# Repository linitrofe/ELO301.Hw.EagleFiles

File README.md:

# ELO301.Hw.EagleFiles
Repositorio dedicado a compartir archivos con el curso ELO301 dictado por el Departamento de Ingeniería Electrónica de la Universidad Técnica Federico Santa María
Se adjunta detalle de los contenidos:
- Carpeta Libraries/ contiene librerías de Autodesk Eagle provistas para su uso en el ramo.

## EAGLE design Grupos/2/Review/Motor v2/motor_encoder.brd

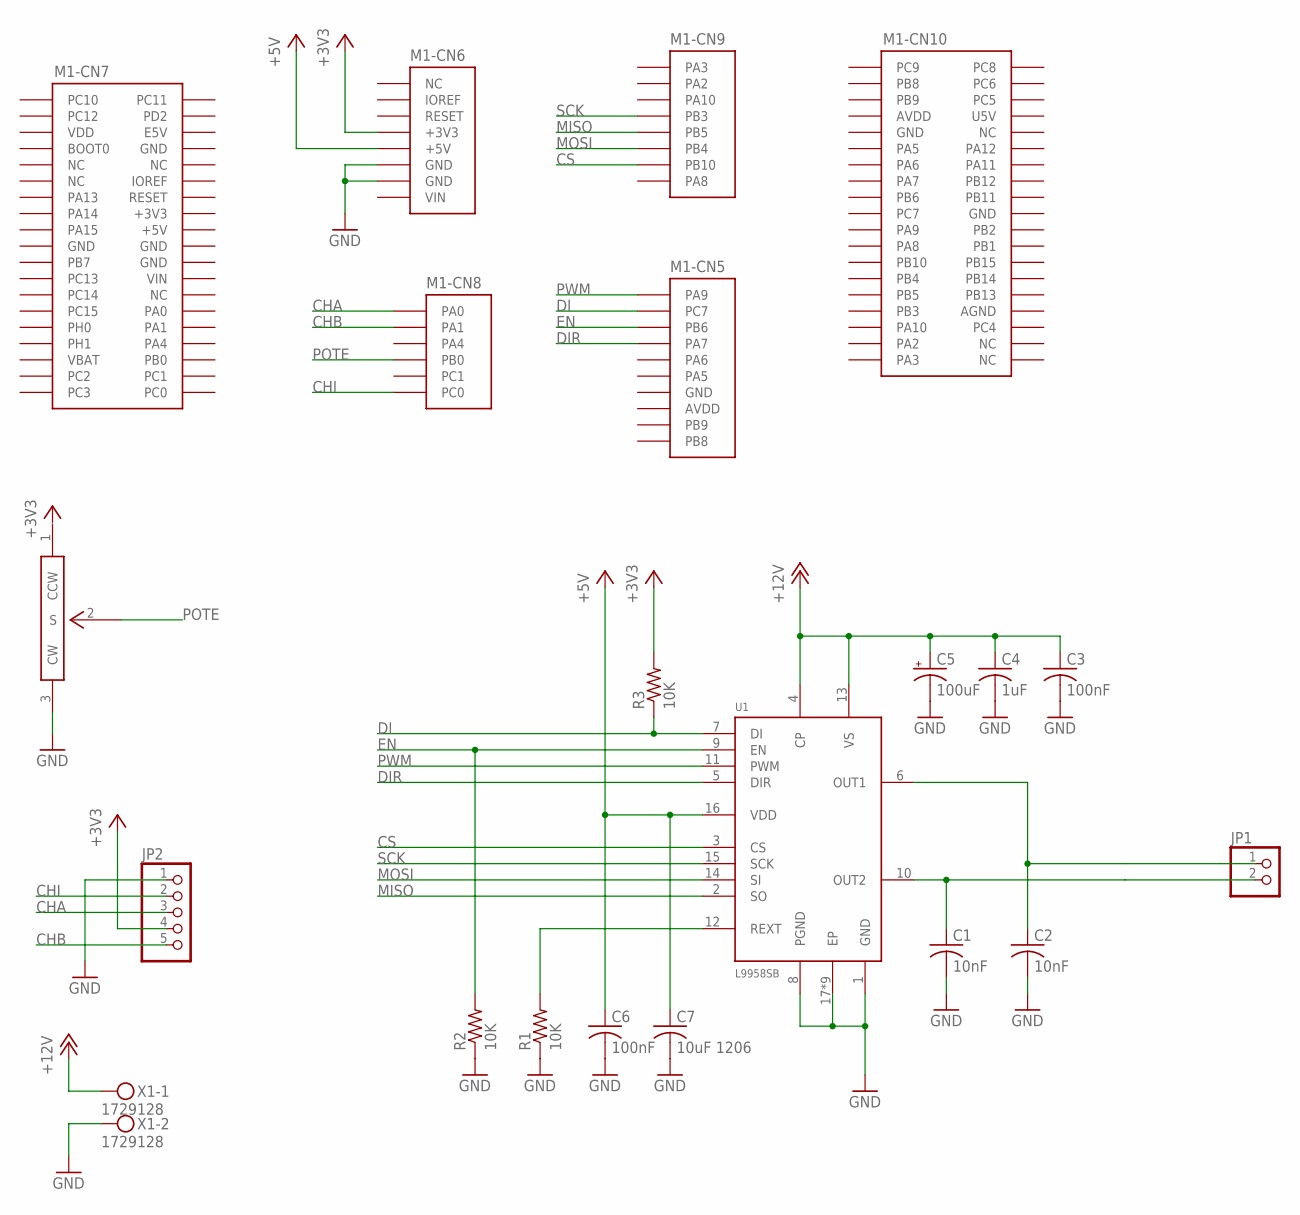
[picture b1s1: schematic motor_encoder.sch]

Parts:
C1, C2: 10nF; C0805; PARTNO GRM2195C1H103JA01D
C3, C6: 100nF; C0805; PARTNO GCM21BR72A104KA37L
C4: 1uF; C0805; PARTNO GCJ219R71C105KA01D
C5: 100uF; F80-UNITE_CHEMI-CON; PARTNO EMVE250ADA101MF80G
C7: 10uF 1206; C1206
JP1: PINHD-1X2; 1X02
JP2: PINHD-1X5; 1X05
M1: NUCLEO-L452RE; NUCLEO-64
R1, R2, R3: 10K; R0805; PARTNO RC0805FR-0710KL
U1: L9958SB; POWERSO-16; PARTNO L9958SB
VR1: P160KN-0QD15B10K; PARTNO P160KN-0QD15B10K
X1: 1729128; MKDSN1,5/2-5,08; PARTNO 1729128

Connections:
+3V3: JP2.4, M1.CN6-4 (+3V3), M1.CN7-16 (+3V3), R3.2
+5V: C6.1, C7.1, M1.CN6-5 (+5V), M1.CN7-18 (+5V), U1.16 (VDD)
+12V: C3.1, C4.1, C5.1 (+), U1.4 (CP), U1.13 (VS), X1.1
AGND: M1.CN10-32 (AGND)
AVDD: M1.CN5-8 (AVDD), M1.CN10-7 (AVDD)
CHA: JP2.3, M1.CN8-1 (PA0)
CHB: JP2.5, M1.CN8-2 (PA1)
CHI: JP2.2, M1.CN8-6 (PC0)
CS: M1.CN9-7 (PB10), U1.3 (CS)
DI: M1.CN5-2 (PC7), R3.1, U1.7 (DI)
DIR: M1.CN5-4 (PA7), U1.5 (DIR)
EN: M1.CN5-3 (PB6), R2.2, U1.9 (EN)
GND: C1.2, C2.2, C3.2, C4.2, C5.2 (-), C6.2, C7.2, JP2.1, M1.CN5-7 (GND), M1.CN6-6 (GND), M1.CN6-7 (GND), M1.CN7-8 (GND), M1.CN7-19 (GND), M1.CN7-20 (GND), M1.CN7-22 (GND), M1.CN10-9 (GND), M1.CN10-20 (GND), R1.1, R2.1, U1.1 (GND), U1.8 (PGND), U1.17 (EP), U1.18 (EP), U1.19 (EP), U1.20 (EP), U1.21 (EP), U1.22 (EP), U1.23 (EP), U1.24 (EP), U1.25 (EP), VR1.3 (CW), X1.2
IOREF: M1.CN6-2 (IOREF)
MISO: M1.CN9-5 (PB5), U1.2 (SO)
MOSI: M1.CN9-6 (PB4), U1.14 (SI)
unnamed: C1.1, JP1.2, U1.10 (OUT2)
unnamed: C2.1, JP1.1, U1.6 (OUT1)
unnamed: R1.2, U1.12 (REXT)
POTE: M1.CN8-4 (PB0), VR1.2 (S)
PWM: M1.CN5-1 (PA9), U1.11 (PWM)
SCK: M1.CN9-4 (PB3), U1.15 (SCK)
U5V: M1.CN10-8 (U5V)
VBAT: M1.CN7-33 (VBAT)
VDD: M1.CN7-5 (VDD)
VIN: M1.CN6-8 (VIN), M1.CN7-24 (VIN)

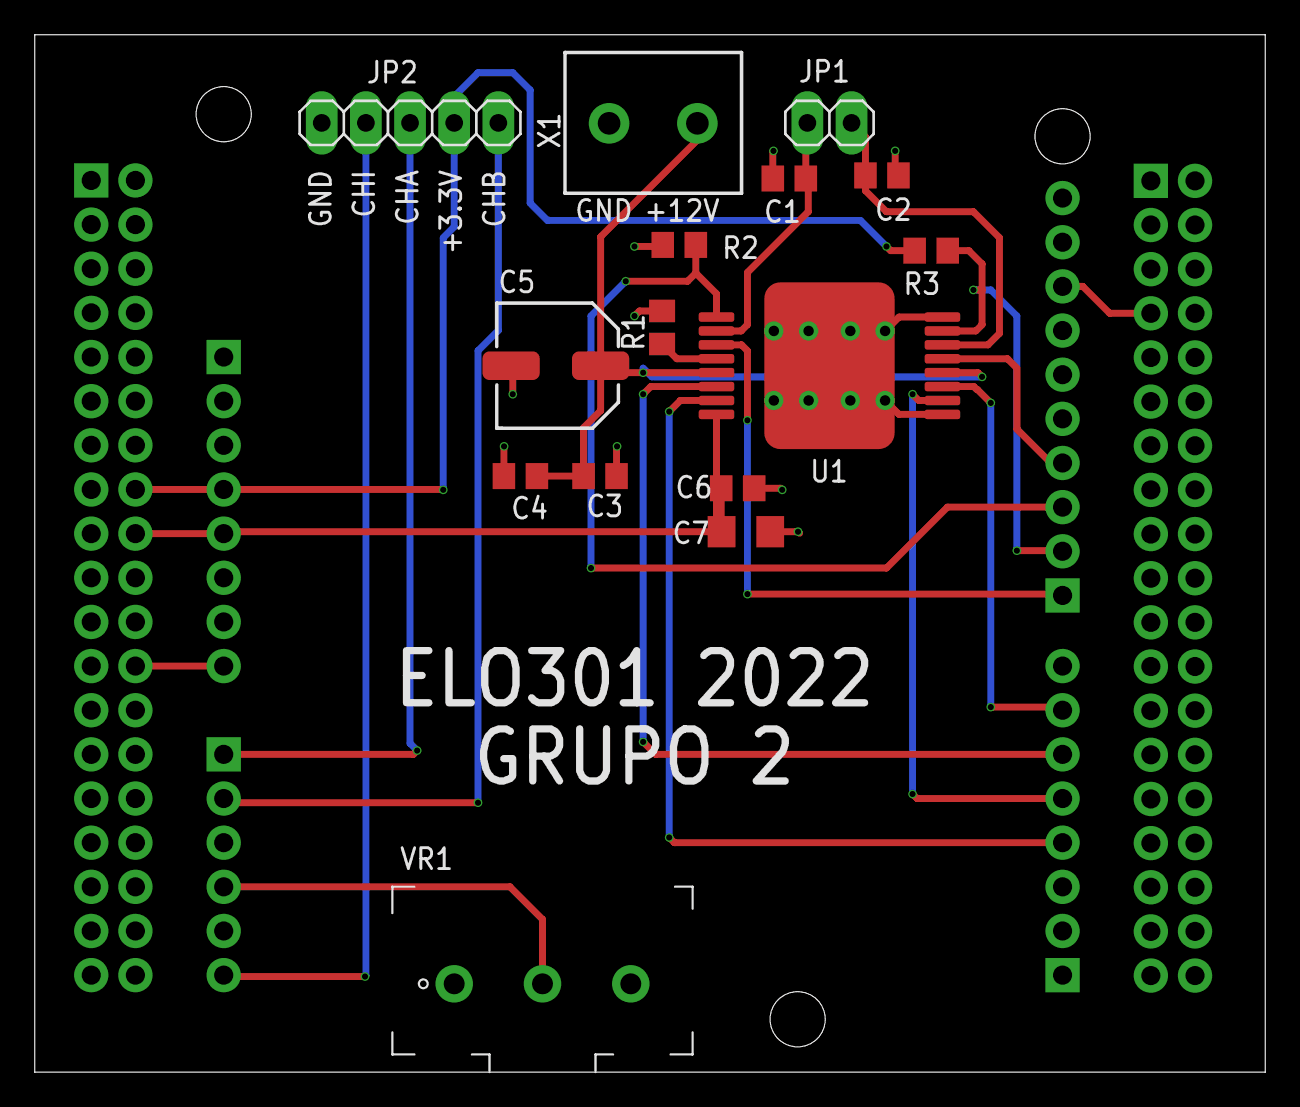
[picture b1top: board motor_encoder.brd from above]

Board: 2 copper layers, 70.8 x 59.7 mm, 16 parts (0 on the bottom side), 21 nets.

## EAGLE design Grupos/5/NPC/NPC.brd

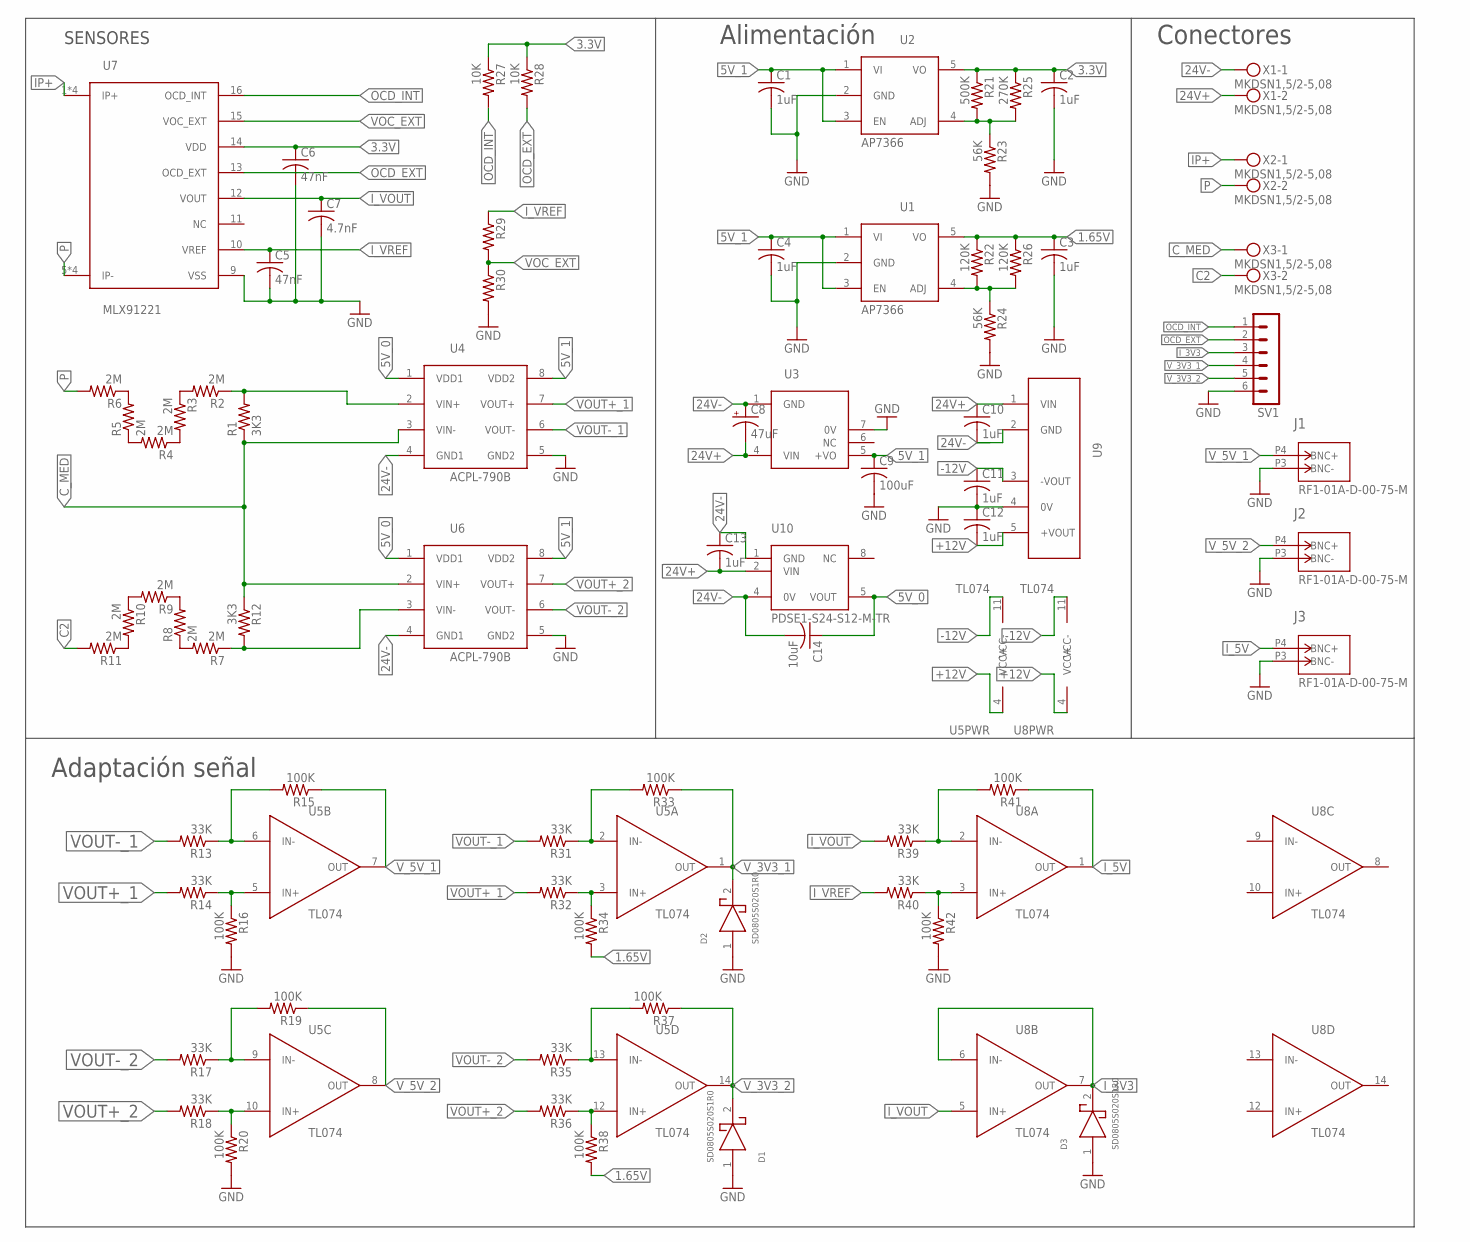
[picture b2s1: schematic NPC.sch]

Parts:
C1, C2, C3, C4, C10, C11, C12, C13: 1uF; C0805; PARTNO GRM219R61H105KA73D
C5, C6: 47nF; C0805; PARTNO CC0805JRX7R7BB473
C7: 4.7nF; C0805; PARTNO 0805ZC472KAT2A
C8: 47uF; 175TMP-0808; PARTNO HHXC630ARA470MHA0G
C9: 100uF; C0805; PARTNO GRM21BR60J107ME15L
C14: 10uF; C0805; PARTNO GRM21BC71C106KE11L
D1, D2, D3: SD0805S020S1R0; 0805; PARTNO SD0805S020S1R0
J1, J2, J3: RF1-01A-D-00-75-M; BNC; PARTNO RF1-01A-D-00-75-M
R1, R12: 3K3; R1206; PARTNO ERJ-S08F3301V
R2, R3, R4, R5, R6, R7, R8, R9, R10, R11: 2M; R1206; PARTNO RCV12062M00FKEA
R13, R14, R17, R18, R31, R32, R35, R36, R39, R40: 33K; M0805; PARTNO CR0805-FX-3302ELF
R15, R16, R19, R20, R33, R34, R37, R38, R41, R42: 100K; M0805; PARTNO CR0805-FX-1003ELF
R21: 500K; M0805; PARTNO CR0805-FX-4993ELF
R22, R26: 120K; M0805; PARTNO CRCW0805120KFKEAC
R23, R24: 56K; M0805; PARTNO CR0805-FX-5602ELF
R25: 270K; M0805; PARTNO CRCW0805270KFKEAC
R27, R28: 10K; M0805; PARTNO CR0805-FX-1002ELF
R29, R30: R-US_M0805; M0805
SV1: MA06-1; PARTNO M20-9750342
U1, U2: AP7366; SOT25; PARTNO AP7366-W5-7
U3: PQP3-D24-S5-M-TR; DIP-5; PARTNO PQP3-D24-S5-M-TR
U4, U6: ACPL-790B; DIP-8; PARTNO ACPL-790B-300E
U5, U8: TL074; SO-14; PARTNO TL074CDT
U7: MLX91221; SOIC-16W; PARTNO MLX91221KDF-ABF-025-RE
U9: PEM2-S24-D12-S; SIP-5; PARTNO PEM2-S24-D12-S
U10: PDSE1-S24-S12-M-TR; PARTNO PQP3-D24-S5-M-TR
X1, X2, X3: MKDSN1,5/2-5,08; PARTNO 1797952

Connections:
1.65V: C3.1, R22.1, R26.1, R34.2, R38.2, U1.5 (VO)
3.3V: C2.1, C6.1, R21.1, R25.1, R27.1, R28.1, U2.5 (VO), U7.14 (VDD)
5V_0: C14.1, U4.1 (VDD1), U6.1 (VDD1), U10.5 (VOUT)
5V_1: C1.1, C4.1, C9.1, U1.1 (VI), U1.3 (EN), U2.1 (VI), U2.3 (EN), U3.5 (+VO), U4.8 (VDD2), U6.8 (VDD2)
24V+: C8.-, C10.1, C13.2, U3.4 (VIN), U9.1 (VIN), U10.2 (VIN), X1.2
24V-: C8.+, C10.2, C13.1, C14.2, U3.1 (GND), U4.4 (GND1), U6.4 (GND1), U9.2 (GND), U10.1 (GND), U10.4 (0V), X1.1
+12V: C12.2, U5.4 (VCC+), U8.4 (VCC+), U9.5 (+VOUT)
-12V: C11.1, U5.11 (VCC-), U8.11 (VCC-), U9.3 (-VOUT)
C2: R11.2, X3.2
C_MED: R1.1, R12.1, U4.3 (VIN-), U6.2 (VIN+), X3.1
GND: C1.2, C2.2, C3.2, C4.2, C5.2, C6.2, C7.2, C9.2, C11.2, C12.1, D1.1 (D+), D2.1 (D+), D3.1 (D+), J1.P3 (BNC-), J2.P3 (BNC-), J3.P3 (BNC-), R16.2, R20.2, R23.2, R24.2, R30.2, R42.2, SV1.6, U1.2 (GND), U2.2 (GND), U3.7 (0V), U4.5 (GND2), U6.5 (GND2), U7.9 (VSS), U9.4 (0V)
IP+: U7.1 (IP+), U7.2 (IP+), U7.3 (IP+), U7.4 (IP+), X2.1
I_3V3: D3.2 (D-), SV1.3, U8.6 (IN-), U8.7 (OUT)
I_5V: J3.P4 (BNC+), R41.1, U8.1 (OUT)
I_VOUT: C7.1, R39.2, U7.12 (VOUT), U8.5 (IN+)
I_VREF: C5.1, R29.1, R40.2, U7.10 (VREF)
unnamed: R2.2, R3.1
unnamed: R3.2, R4.1
unnamed: R4.2, R5.1
unnamed: R5.2, R6.1
unnamed: R7.2, R8.1
unnamed: R8.2, R9.1
unnamed: R9.2, R10.1
unnamed: R10.2, R11.1
unnamed: R32.1, R34.1, U5.3 (IN+)
unnamed: R7.1, R12.2, U6.3 (VIN-)
unnamed: R18.1, R20.1, U5.10 (IN+)
unnamed: R17.1, R19.2, U5.9 (IN-)
unnamed: R21.2, R23.1, R25.2, U2.4 (ADJ)
unnamed: R22.2, R24.1, R26.2, U1.4 (ADJ)
unnamed: R14.1, R16.1, U5.5 (IN+)
unnamed: R13.1, R15.2, U5.6 (IN-)
unnamed: R1.2, R2.1, U4.2 (VIN+)
unnamed: R31.1, R33.2, U5.2 (IN-)
unnamed: R36.1, R38.1, U5.12 (IN+)
unnamed: R35.1, R37.2, U5.13 (IN-)
unnamed: R40.1, R42.1, U8.3 (IN+)
unnamed: R39.1, R41.2, U8.2 (IN-)
OCD_EXT: R28.2, SV1.2, U7.13 (OCD_EXT)
OCD_INT: R27.2, SV1.1, U7.16 (OCD_INT)
P: R6.2, U7.5 (IP-), U7.6 (IP-), U7.7 (IP-), U7.8 (IP-), X2.2
VOC_EXT: R29.2, R30.1, U7.15 (VOC_EXT)
VOUT+_1: R14.2, R32.2, U4.7 (VOUT+)
VOUT+_2: R18.2, R36.2, U6.7 (VOUT+)
VOUT-_1: R13.2, R31.2, U4.6 (VOUT-)
VOUT-_2: R17.2, R35.2, U6.6 (VOUT-)
V_3V3_1: D2.2 (D-), R33.1, SV1.4, U5.1 (OUT)
V_3V3_2: D1.2 (D-), R37.1, SV1.5, U5.14 (OUT)
V_5V_1: J1.P4 (BNC+), R15.1, U5.7 (OUT)
V_5V_2: J2.P4 (BNC+), R19.1, U5.8 (OUT)

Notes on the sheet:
SENSORES
Alimentación
Conectores
Adaptación señal

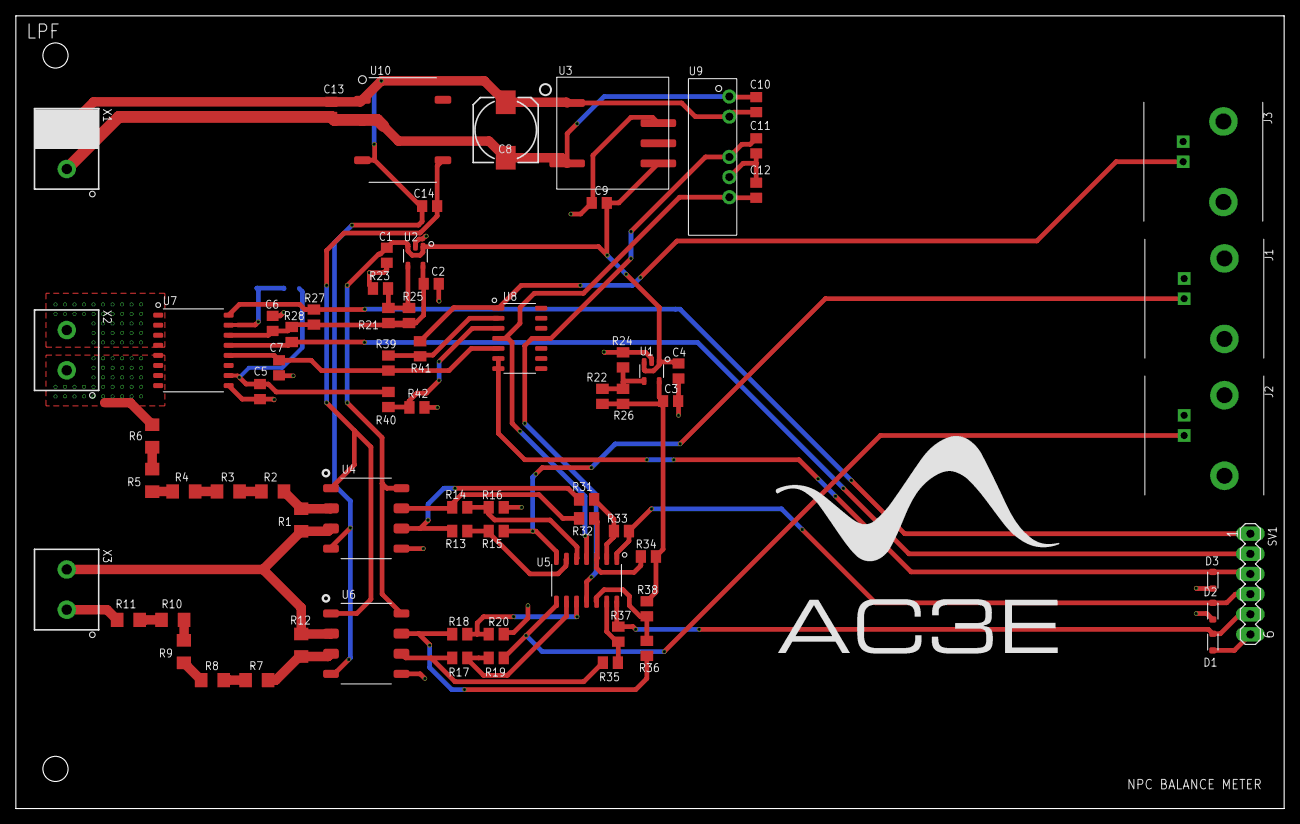
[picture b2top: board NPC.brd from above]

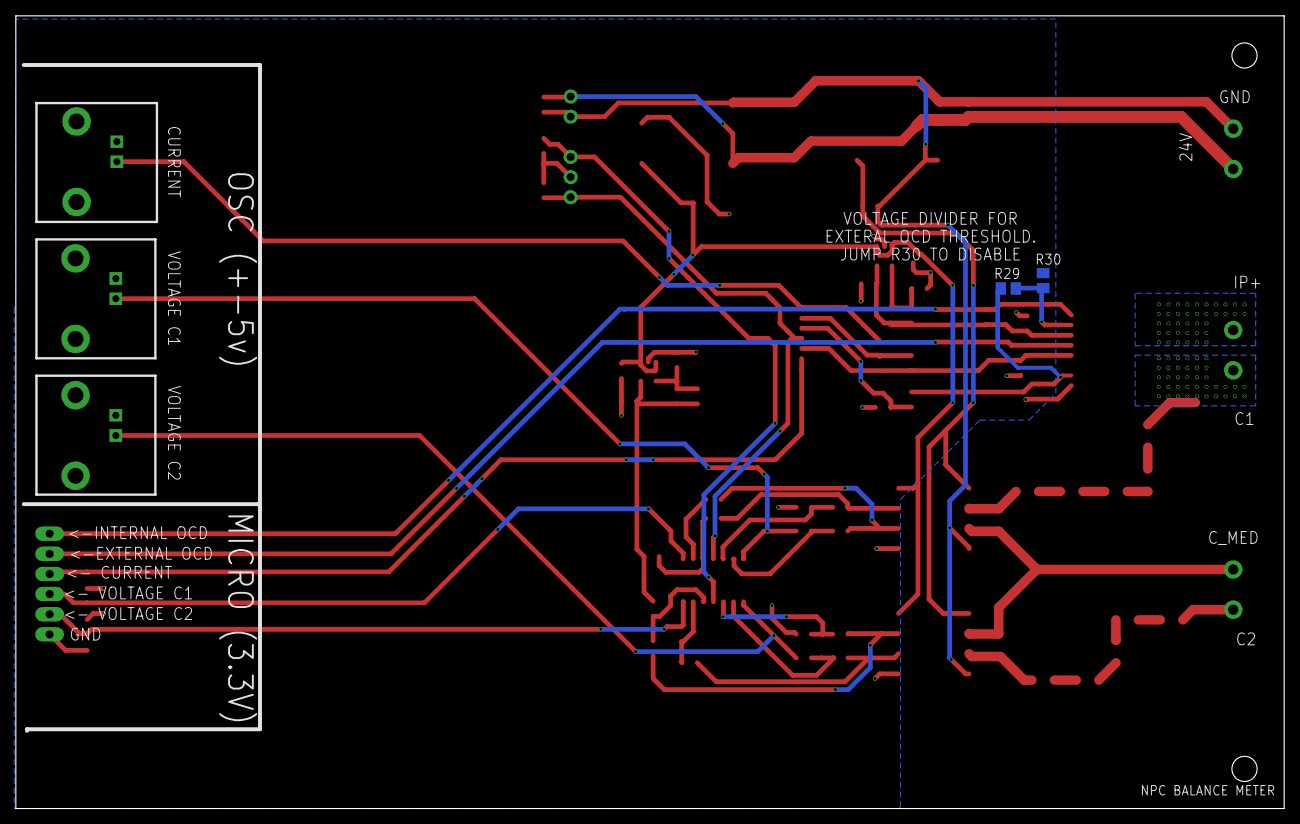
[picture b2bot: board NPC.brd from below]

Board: 2 copper layers, 160.0 x 100.0 mm, 76 parts (2 on the bottom side), 50 nets.

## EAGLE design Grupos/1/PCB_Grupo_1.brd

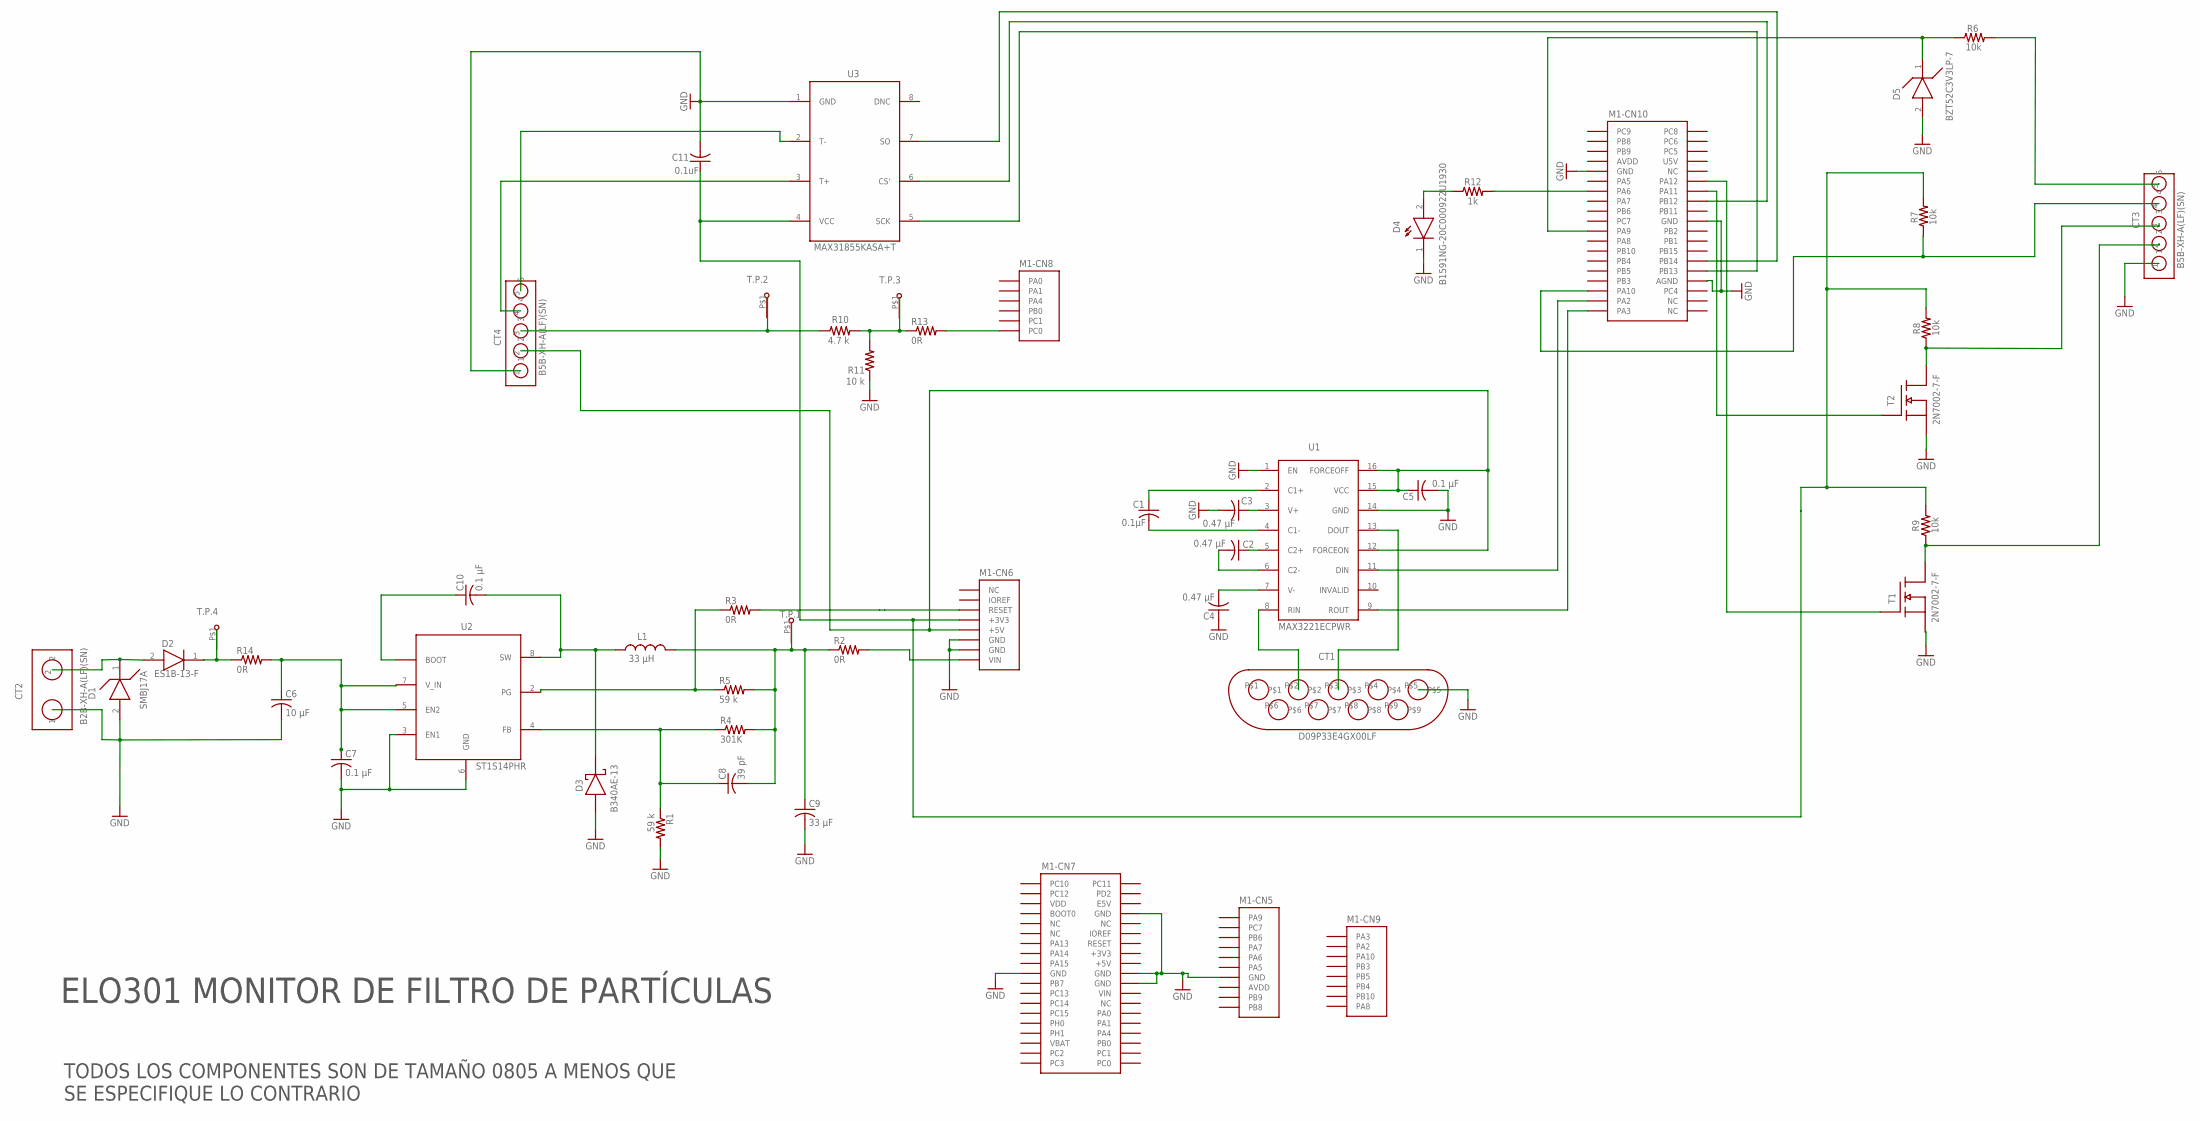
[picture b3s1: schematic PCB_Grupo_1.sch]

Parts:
C1: 0.1μF; C0805; PARTNO GCM21BR72A104KA37L
C2, C3, C4: 0.47 μF; C0805; PARTNO GCM21BR71H474KA55L
C5: 0.1 μF; C0805; PARTNO GCM21BR72A104KA37L
C6: 10 μF; C0805; PART_NO GRM21BR61H106KE43L
C7, C10: 0.1 μF; C0805; PART_NO GCM21BR72A104KA37L
C8: 39 pF; C0805; PART_NO GRM21A5C2E390JW01D
C9: 33 μF; C0805; PART_NO GRM21BR60G336ME15L
C11: 0.1uF; C0805; PART_NO GCM21BR72A104KA37L
CT1: D09P33E4GX00LF; JEDEC; PART_NO D09P33E4GX00LF
CT2: B2B-XH-A(LF)(SN); 2-PIN-XH-JST; PART_NO B2B-XH-A(LF)(SN)
CT3: B5B-XH-A(LF)(SN); 5-PIN-JST; PARTNO B5B-XH-A(LF)(SN)
CT4: B5B-XH-A(LF)(SN); 5-PIN-JST; PART_NO B5B-XH-A(LF)(SN)
D1: SMBJ17A; DO-214AA; PART_NO SMBJ17A
D2: ES1B-13-F; DO-214AC; PART_NO ES1B-13-F
D3: B340AE-13; DO-214AC; PART_NO B340AE-13
D4: B1591NG-20C000922U1930; 1206(3216METRIC); PART_NO B1591NG-20C000922U1930
D5: BZT52C3V3LP-7; 0402; PART_NO BZT52C3V3LP-7
L1: 33 μH; SMD; PART_NO LVS606045-330M-N
M1: NUCLEO-L452RE; NUCLEO-64
R1, R5: 59 k; R0805; PART_NO RC0805FR-0759KL
R2, R3, R13, R14: 0R; R0805; PART_NO RC0805JR-070RL
R4: 301K; R0805; PARTNO RC0805FR-07301KL
R6, R7, R8, R9: 10k; R0805; PARTNO Y40227K34000T9W
R10: 4.7 k; R0805; PART_NO RC0805FR-074K7L
R11: 10 k; R0805; PART_NO RC0805FR-0710KL
R12: 1k; R0805; PART_NO RC0805FR-071KL
T1, T2: 2N7002-7-F; TO-236-3; PART_NO 2N7002-7-F
T.P.1, T.P.2, T.P.3, T.P.4: TEST_POINT; T.P.
U1: MAX3221ECPWR; TSSOP; PART_NO MAX3221ECPWR
U2: ST1S14PHR; 8-SOIC; PART_NO ST1S14PHR
U3: MAX31855KASA+T; 8-SOIC; PART_NO MAX31855KASA+T

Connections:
+3V3: M1.CN7-16 (+3V3)
+5V: M1.CN7-18 (+5V)
AVDD: M1.CN5-8 (AVDD), M1.CN10-7 (AVDD)
GND: C3.2, C4.1, C5.2, C6.2, C7.2, C9.2, C11.2, CT1.P$5, CT2.1, CT3.1, CT4.1, D1.2 (A), D3.2 (ANODO), D4.1 (C), D5.2 (A), M1.CN5-7 (GND), M1.CN6-6 (GND), M1.CN6-7 (GND), M1.CN7-8 (GND), M1.CN7-19 (GND), M1.CN7-20 (GND), M1.CN7-22 (GND), M1.CN10-9 (GND), M1.CN10-20 (GND), M1.CN10-32 (AGND), R1.2, R11.1, T1.S (SOURCE), T2.S (SOURCE), U1.1 (EN), U1.14 (GND), U2.3 (EN1), U2.6 (GND), U3.1 (GND)
IOREF: M1.CN6-2 (IOREF)
unnamed: C1.1, U1.2 (C1+)
unnamed: C3.1, U1.3 (V+)
unnamed: C1.2, U1.4 (C1-)
unnamed: C2.1, U1.5 (C2+)
unnamed: C2.2, U1.6 (C2-)
unnamed: C4.2, U1.7 (V-)
unnamed: CT1.P$2, U1.8 (RIN)
unnamed: C5.1, CT4.2, M1.CN6-5 (+5V), U1.12 (FORCEON), U1.15 (VCC), U1.16 (FORCEOFF)
unnamed: CT1.P$3, U1.13 (DOUT)
unnamed: CT2.2, D1.1 (C), D2.2 (A)
unnamed: C6.1, C7.1, R14.2, U2.5 (EN2), U2.7 (V_IN)
unnamed: C10.1, U2.1 (BOOT)
unnamed: C10.2, D3.1 (CATODO), L1.1, U2.8 (SW)
unnamed: C8.1, R1.1, R4.1, U2.4 (FB)
unnamed: C8.2, C9.1, L1.2, R2.1, R4.2, R5.2, T.P.1.P$1
unnamed: R3.1, R5.1, U2.2 (PG)
unnamed: M1.CN6-3 (RESET), R3.2
unnamed: M1.CN6-8 (VIN), R2.2
unnamed: M1.CN10-14 (PA11), T2.G (GATE)
unnamed: CT3.4, M1.CN10-33 (PA10), R7.1
unnamed: M1.CN10-12 (PA12), T1.G (GATE)
unnamed: CT3.5, R6.2
unnamed: D5.1 (C), M1.CN10-21 (PA9), R6.1
unnamed: CT3.3, R8.1, T2.D (DRAIN)
unnamed: D4.2 (A), R12.1
unnamed: C11.1, M1.CN6-4 (+3V3), R7.2, R8.2, R9.2, U3.4 (VCC)
unnamed: CT3.2, R9.1, T1.D (DRAIN)
unnamed: CT4.4, U3.3 (T+)
unnamed: CT4.5, U3.2 (T-)
unnamed: M1.CN10-28 (PB14), U3.7 (SO)
unnamed: M1.CN10-16 (PB12), U3.6 (CS')
unnamed: M1.CN10-30 (PB13), U3.5 (SCK)
unnamed: M1.CN10-35 (PA2), U1.11 (DIN)
unnamed: R10.2, R11.2, R13.1, T.P.3.P$1
unnamed: M1.CN10-37 (PA3), U1.9 (ROUT)
unnamed: M1.CN10-13 (PA6), R12.2
unnamed: M1.CN8-6 (PC0), R13.2
unnamed: CT4.3, R10.1, T.P.2.P$1
unnamed: D2.1 (C), R14.1, T.P.4.P$1
U5V: M1.CN10-8 (U5V)
VBAT: M1.CN7-33 (VBAT)
VDD: M1.CN7-5 (VDD)
VIN: M1.CN7-24 (VIN)

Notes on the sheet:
TODOS LOS COMPONENTES SON DE TAMAÑO 0805 A MENOS QUE SE ESPECIFIQUE LO CONTRARIO
ELO301 MONITOR DE FILTRO DE PARTÍCULAS

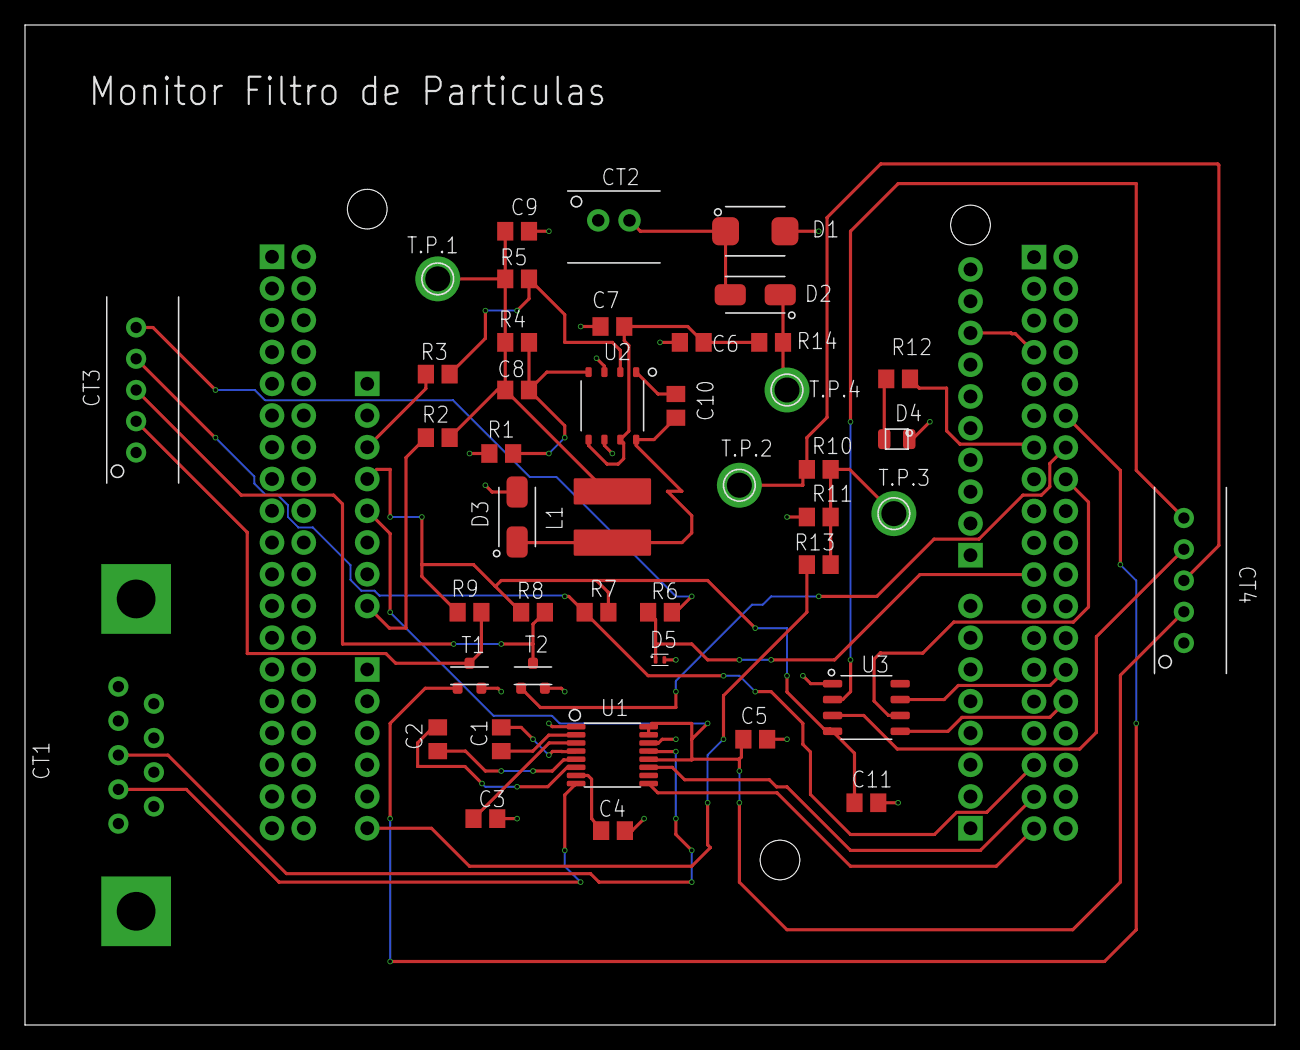
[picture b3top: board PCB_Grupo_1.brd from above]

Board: 2 copper layers, 100.0 x 80.0 mm, 45 parts (0 on the bottom side), 41 nets.

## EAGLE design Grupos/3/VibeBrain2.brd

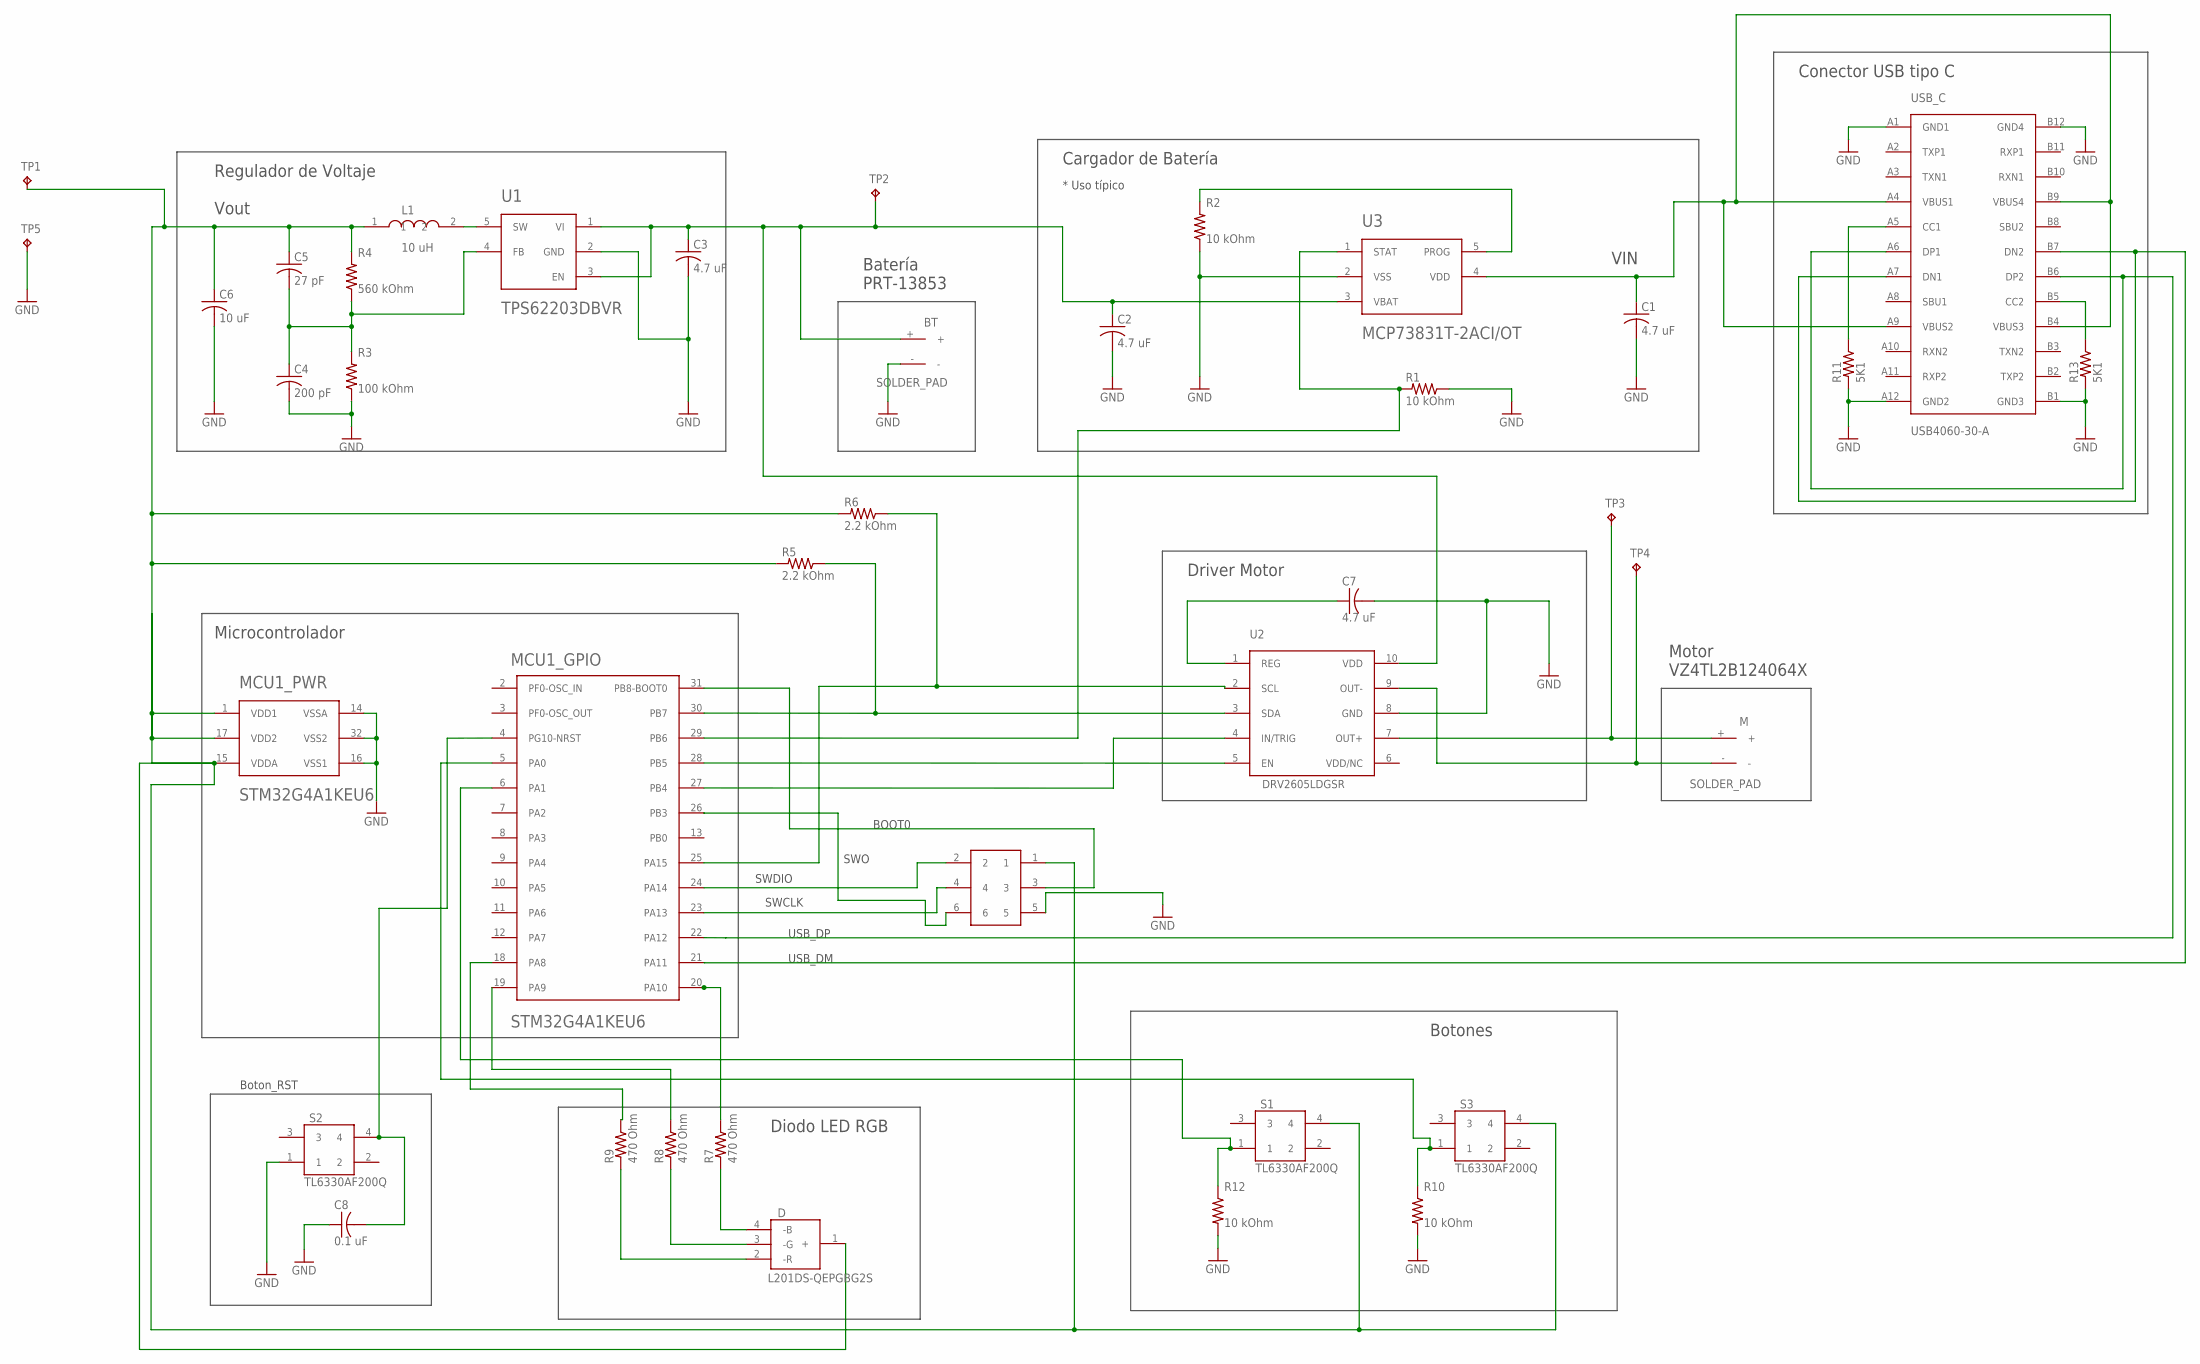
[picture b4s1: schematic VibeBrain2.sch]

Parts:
BT: SOLDER_PAD; SMD
C1, C2, C3, C7: 4.7 uF; C0402; PARTNO GRM155R60J475ME47J
C4: 200 pF; C0402; PARTNO GCM1555C1H201FA16D
C5: 27 pF; C0402; PARTNO GCM1555C1H270JA16D
C6: 10 uF; C0402; PARTNO GRM155R60J106ME05J
C8: 0.1 uF; C0402; PARTNO GCM155R71C104KA55J
D: L201DS-QEPGBG2S; SMD; PARTNO L201DS-QEPGBG2S
J1: TC2030-IDC; TC2030-IDC-FP; PARTNO TC2030-IDC
L1: 10 uH; SMD; PARTNO LQW15DN100M00D
M: SOLDER_PAD; SMD
MCU1: STM32G4A1KEU6; 32-UFQFPN(5X5); PARTNO STM32G4A1KEU6
R1, R2, R10, R12: 10 kOhm; R0402; PARTNO RMCF0402FT10K0
R3: 100 kOhm; R0402; PARTNO RMCF0402FT100K
R4: 560 kOhm; R0402; PARTNO ERJ-2RKF5603X
R5, R6: 2.2 kOhm; R0402; PARTNO RMCF0402JT2K20
R7, R8, R9: 470 Ohm; R0402; PARTNO RMCF0402FT470R
R11, R13: 5K1; R0402; PARTNO RC0402FR-075K1L
S1, S2, S3: TL6330AF200Q; SWITCH; PARTNO TL6330AF200Q
TP1, TP2, TP3, TP4, TP5: TPTP07SQ; TP07SQ
U1: TPS62203DBVR; SOT-23-5; PARTNO TPS62203DBVR
U2: DRV2605LDGSR; 10-VSSOP; PARTNO DRV2605LDGSR
U3: MCP73831T-2ACI/OT; SOT-23-5; PARTNO MCP73831T-2ACI/OT
USB_C: USB4060-30-A; USB_C; PARTNO USB4060-30-A

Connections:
A2: C7.1, U2.1 (REG)
FB: C4.1, C5.2, R3.2, R4.1, U1.4 (FB)
GND: BT.-, C1.2, C2.2, C3.2, C4.2, C6.2, C7.2, C8.1, J1.5, MCU1.14 (VSSA), MCU1.16 (VSS1), MCU1.32 (VSS2), R1.1, R2.1, R3.1, R10.2, R11.2, R12.2, R13.2, S2.1, TP5.TP, U1.2 (GND), U2.8 (GND), U3.2 (VSS), USB_C.A1 (GND1), USB_C.A12 (GND2), USB_C.B1 (GND3), USB_C.B12 (GND4)
unnamed: MCU1.30 (PB7), R5.1, U2.3 (SDA)
unnamed: MCU1.29 (PB6), R1.2, U3.1 (STAT)
unnamed: J1.3, MCU1.31 (PB8-BOOT0)
unnamed: MCU1.28 (PB5), U2.5 (EN)
unnamed: MCU1.27 (PB4), U2.4 (IN/TRIG)
unnamed: M.+, TP3.TP, U2.7 (OUT+)
unnamed: M.-, TP4.TP, U2.9 (OUT-)
unnamed: MCU1.22 (PA12), USB_C.A6 (DP1), USB_C.B6 (DP2)
unnamed: MCU1.19 (PA9), R8.1
unnamed: MCU1.21 (PA11), USB_C.A7 (DN1), USB_C.B7 (DN2)
unnamed: MCU1.5 (PA0), R10.1, S3.1
unnamed: MCU1.6 (PA1), R12.1, S1.1
unnamed: MCU1.20 (PA10), R7.1
unnamed: J1.2, MCU1.24 (PA14)
unnamed: D.4 (-B), R7.2
unnamed: D.3 (-G), R8.2
unnamed: D.2 (-R), R9.2
unnamed: J1.6, MCU1.26 (PB3)
unnamed: J1.4, MCU1.23 (PA13)
unnamed: MCU1.25 (PA15), R6.1, U2.2 (SCL)
unnamed: L1.2, U1.5 (SW)
unnamed: C8.2, MCU1.4 (PG10-NRST), S2.4
unnamed: MCU1.18 (PA8), R9.1
unnamed: R11.1, USB_C.A5 (CC1)
unnamed: R13.1, USB_C.B5 (CC2)
PROG: R2.2, U3.5 (PROG)
REG_OUT: C5.1, C6.1, D.1 (+), J1.1, L1.1, MCU1.1 (VDD1), MCU1.15 (VDDA), MCU1.17 (VDD2), R4.2, R5.2, R6.2, S1.4, S3.4, TP1.TP
VBAT: BT.+, C2.1, C3.1, TP2.TP, U1.1 (VI), U1.3 (EN), U2.10 (VDD), U3.3 (VBAT)
VDD: C1.1, U3.4 (VDD), USB_C.A4 (VBUS1), USB_C.A9 (VBUS2), USB_C.B4 (VBUS3), USB_C.B9 (VBUS4)
VDD/NC: U2.6 (VDD/NC)

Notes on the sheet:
Batería PRT-13853
VIN
Cargador de Batería
* Uso típico
Regulador de Voltaje
Vout
Motor VZ4TL2B124064X
Microcontrolador
Driver Motor
Botones
Diodo LED RGB
Conector USB tipo C
USB_DP
USB_DM
Boton_RST
SWDIO
SWCLK
BOOT0
SWO

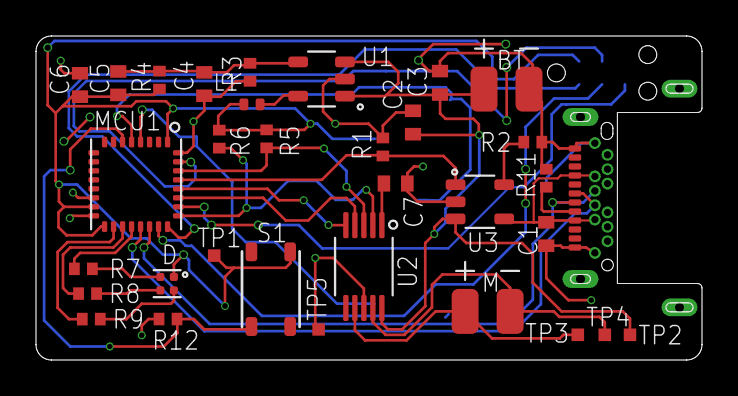
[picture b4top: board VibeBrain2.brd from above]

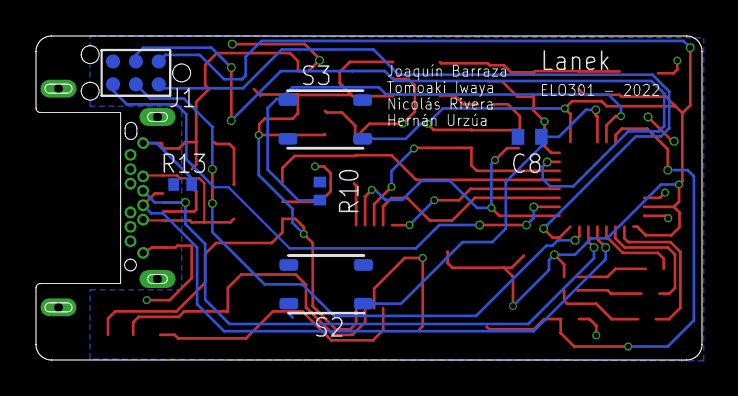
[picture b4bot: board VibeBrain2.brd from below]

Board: 2 copper layers, 37.0 x 18.0 mm, 39 parts (6 on the bottom side), 32 nets.
